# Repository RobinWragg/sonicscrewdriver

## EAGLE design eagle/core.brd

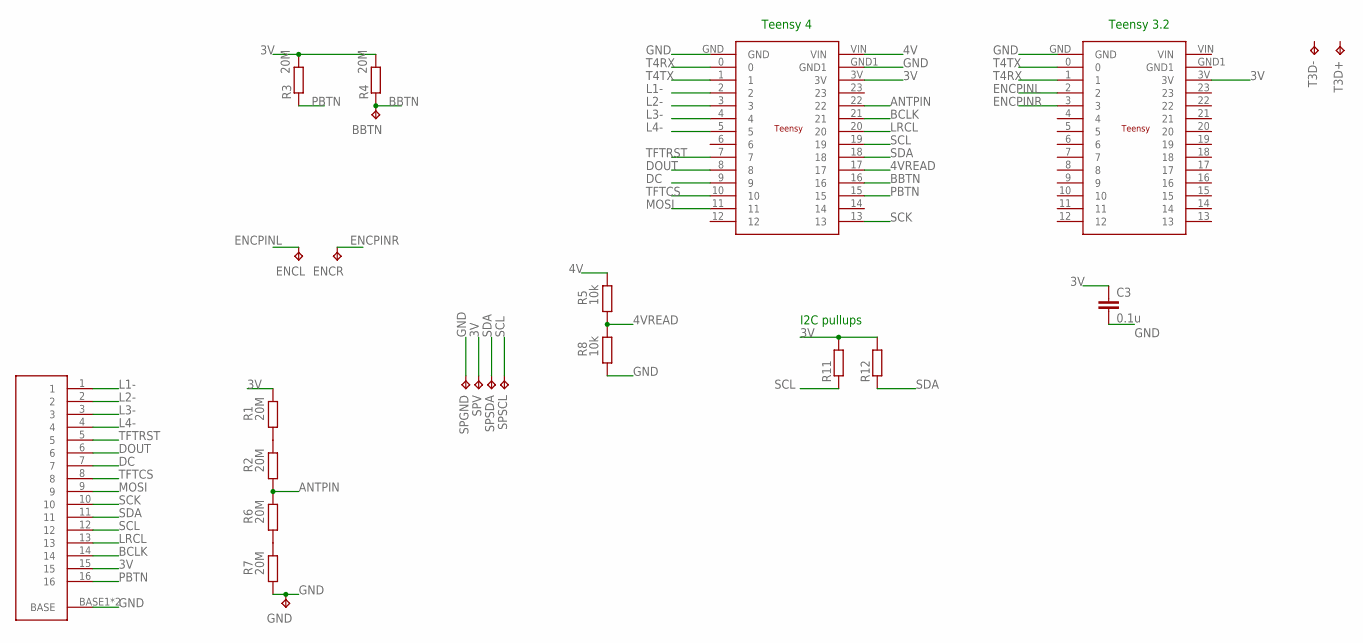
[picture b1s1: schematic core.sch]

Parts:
BBTN: TPTP14R; TP14R
C3: 0.1u; C0805
ENCL: TPTP14R; TP14R
ENCR: TPTP14R; TP14R
GND: TPTP14R; TP14R
R1, R2, R3, R4, R6, R7: 20M; M0805
R5, R8: 10k; M0805
R11, R12: R-EU_R0805; R0805
SPGND: TPTP14R; TP14R
SPSCL: TPTP14R; TP14R
SPSDA: TPTP14R; TP14R
SPV: TPTP14R; TP14R
T3D+, T3D-: TPTP14R; TP14R
U$1: TEENSY4; TEENSYSMALL
U$2: TEENSYSMALL
U$3: 16PINFFC

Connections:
3V: C3.1, R1.2, R3.2, R4.2, R11.2, R12.2, SPV.TP, U$1.3V, U$2.3V, U$3.15
4V: R5.2, U$1.VIN
4VREAD: R5.1, R8.2, U$1.17
ANTPIN: R2.1, R6.2, U$1.22
BBTN: BBTN.TP, R4.1, U$1.16
BCLK: U$1.21, U$3.14
DC: U$1.9, U$3.7
DOUT: U$1.8, U$3.6
ENCPINL: ENCL.TP, U$2.2
ENCPINR: ENCR.TP, U$2.3
GND: C3.2, GND.TP, R7.1, R8.1, SPGND.TP, U$1.GND, U$1.GND1, U$2.GND, U$3.BASE1 (BASE), U$3.BASE2 (BASE)
L1-: U$1.2, U$3.1
L2-: U$1.3, U$3.2
L3-: U$1.4, U$3.3
L4-: U$1.5, U$3.4
LRCL: U$1.20, U$3.13
MOSI: U$1.11, U$3.9
unnamed: R6.1, R7.2
unnamed: R1.1, R2.2
PBTN: R3.1, U$1.15, U$3.16
SCK: U$1.13, U$3.10
SCL: R11.1, SPSCL.TP, U$1.19, U$3.12
SDA: R12.1, SPSDA.TP, U$1.18, U$3.11
T4RX: U$1.0, U$2.1
T4TX: U$1.1, U$2.0
TFTCS: U$1.10, U$3.8
TFTRST: U$1.7, U$3.5

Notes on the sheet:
Teensy 4
Teensy 3.2
I2C pullups

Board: 2 copper layers, 24 parts (12 on the bottom side), 27 nets, no tracks yet.

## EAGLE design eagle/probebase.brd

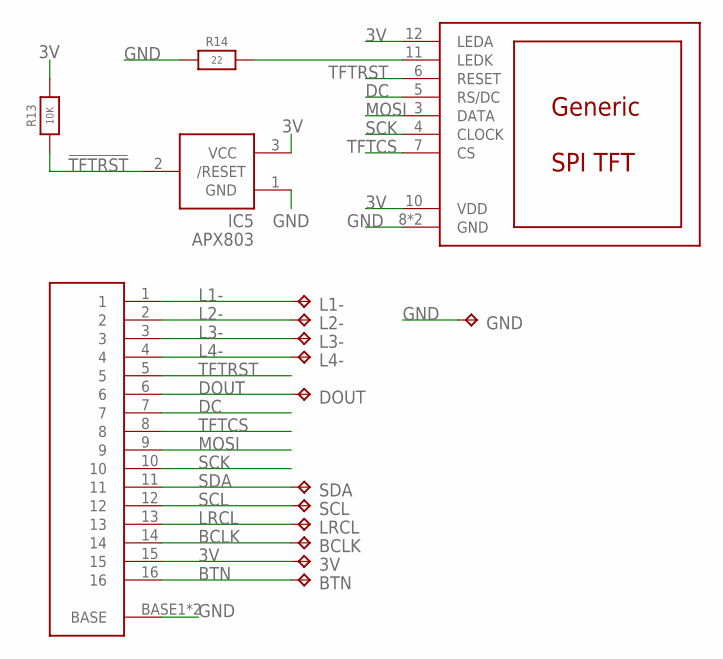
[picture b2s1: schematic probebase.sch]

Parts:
3V: TPTP14R; TP14R
BCLK: TPTP14R; TP14R
BTN: TPTP14R; TP14R
DOUT: TPTP14R; TP14R
GND: TPTP14R; TP14R
IC5: APX803; SOT23
L1-, L2-, L3-, L4-: TPTP14R; TP14R
LRCL: TPTP14R; TP14R
R13: 10K; 0603-NO
R14: 22; 0603-NO
SCL: TPTP14R; TP14R
SDA: TPTP14R; TP14R
U$3: 16PINFFC
U$4: TFT; MICROBUILDER_TFT_1.14IN_240X135_WRAPUNDER

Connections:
3V: 3V.TP, IC5.3 (VCC), R13.2, U$3.15, U$4.10 (VDD), U$4.12 (LEDA)
!TFTRST: IC5.2 (/RESET), R13.1
BCLK: BCLK.TP, U$3.14
BTN: BTN.TP, U$3.16
DC: U$3.7, U$4.5 (RS/DC)
DOUT: DOUT.TP, U$3.6
GND: GND.TP, IC5.1 (GND), R14.1, U$3.BASE1 (BASE), U$3.BASE2 (BASE), U$4.8 (GND), U$4.13 (GND)
L1-: L1-.TP, U$3.1
L2-: L2-.TP, U$3.2
L3-: L3-.TP, U$3.3
L4-: L4-.TP, U$3.4
LRCL: LRCL.TP, U$3.13
MOSI: U$3.9, U$4.3 (DATA)
unnamed: R14.2, U$4.11 (LEDK)
SCK: U$3.10, U$4.4 (CLOCK)
SCL: SCL.TP, U$3.12
SDA: SDA.TP, U$3.11
TFTCS: U$3.8, U$4.7 (CS)
TFTRST: U$3.5, U$4.6 (RESET)

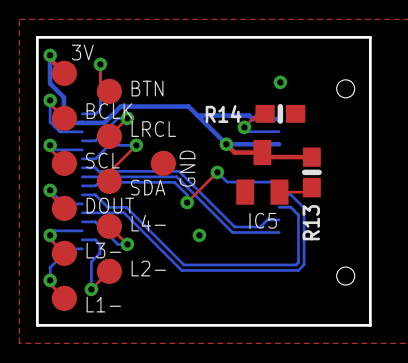
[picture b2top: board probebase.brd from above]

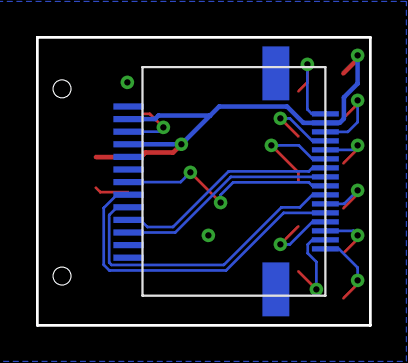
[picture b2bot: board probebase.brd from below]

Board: 2 copper layers, 18.5 x 16.0 mm, 17 parts (2 on the bottom side), 19 nets.

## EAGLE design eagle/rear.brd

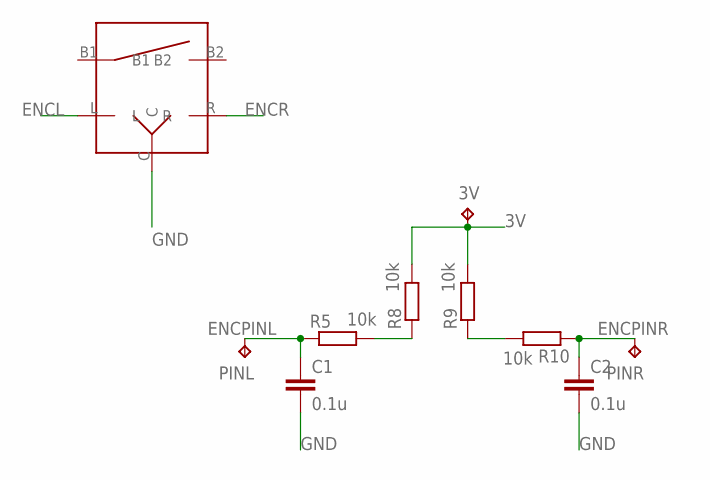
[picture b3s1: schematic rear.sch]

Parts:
3V: TPTP14R; TP14R
C1, C2: 0.1u; C0805
PINL: TPTP14R; TP14R
PINR: TPTP14R; TP14R
R5, R8, R9, R10: 10k; M0805
U$1: ENCODER

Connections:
3V: 3V.TP, R8.2, R9.2
ENCL: R5.2, R8.1, U$1.L
ENCPINL: C1.1, PINL.TP, R5.1
ENCPINR: C2.1, PINR.TP, R10.1
ENCR: R9.1, R10.2, U$1.R
GND: C1.2, C2.2, U$1.C

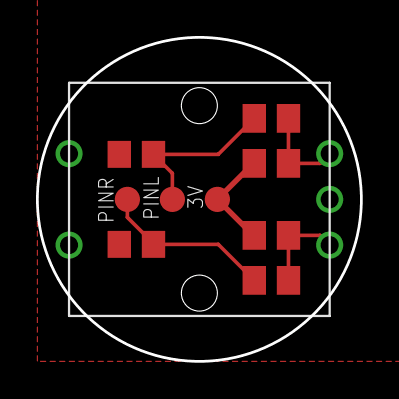
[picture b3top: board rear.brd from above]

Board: 2 copper layers, 18.0 x 18.0 mm, 10 parts (0 on the bottom side), 6 nets.

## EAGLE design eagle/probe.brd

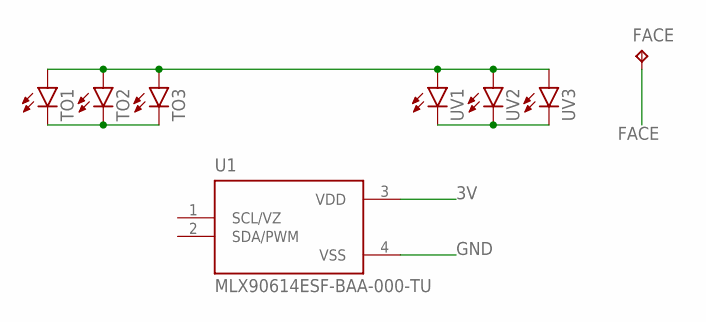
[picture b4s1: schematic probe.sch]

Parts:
FACE: TPTP14R; TP14R
TO1, TO2, TO3: LED5MM
U1: MLX90614ESF-BAA-000-TU; TO254P942H425-4
UV1, UV2, UV3: LED5MM

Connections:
3V: TO1.A, TO2.A, TO3.A, U1.3 (VDD), UV1.A, UV2.A, UV3.A
FACE: FACE.TP
GND: U1.4 (VSS)
unnamed: TO1.K (C), TO2.K (C), TO3.K (C)
unnamed: UV1.K (C), UV2.K (C), UV3.K (C)

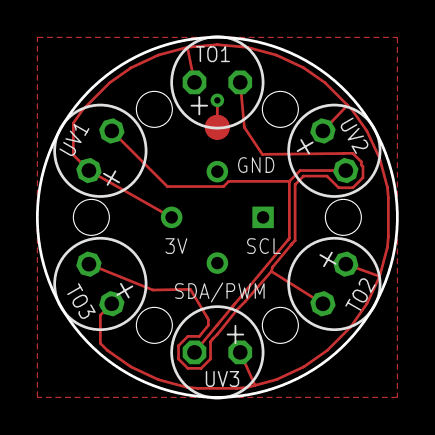
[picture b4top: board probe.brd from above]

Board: 2 copper layers, 20.0 x 20.0 mm, 8 parts (1 on the bottom side), 3 nets.

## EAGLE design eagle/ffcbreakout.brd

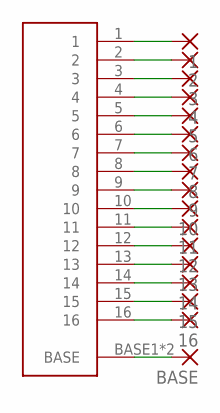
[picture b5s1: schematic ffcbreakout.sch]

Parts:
1, 2, 3, 4, 5, 6, 7, 8, 9, 10, 11, 12, 13, 14, 15, 16: 1,6/0,8
BASE: 1,6/0,8
U$1: 16PINFFC

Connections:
unnamed: 1.1, U$1.1
unnamed: 2.1, U$1.2
unnamed: 3.1, U$1.3
unnamed: 4.1, U$1.4
unnamed: 5.1, U$1.5
unnamed: 6.1, U$1.6
unnamed: 7.1, U$1.7
unnamed: 8.1, U$1.8
unnamed: 9.1, U$1.9
unnamed: 10.1, U$1.10
unnamed: 11.1, U$1.11
unnamed: 12.1, U$1.12
unnamed: 13.1, U$1.13
unnamed: 14.1, U$1.14
unnamed: 15.1, U$1.15
unnamed: 16.1, U$1.16
unnamed: BASE.1, U$1.BASE1 (BASE), U$1.BASE2 (BASE)

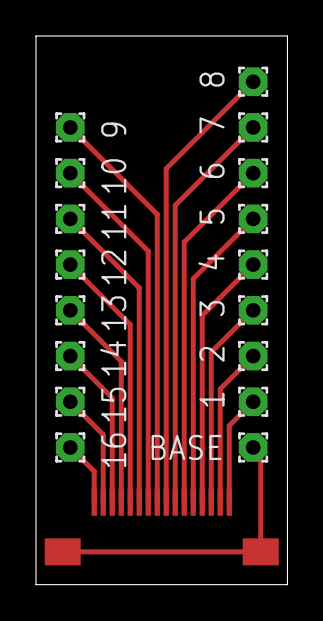
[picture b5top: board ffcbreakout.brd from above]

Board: 2 copper layers, 14.0 x 30.5 mm, 18 parts (0 on the bottom side), 17 nets.

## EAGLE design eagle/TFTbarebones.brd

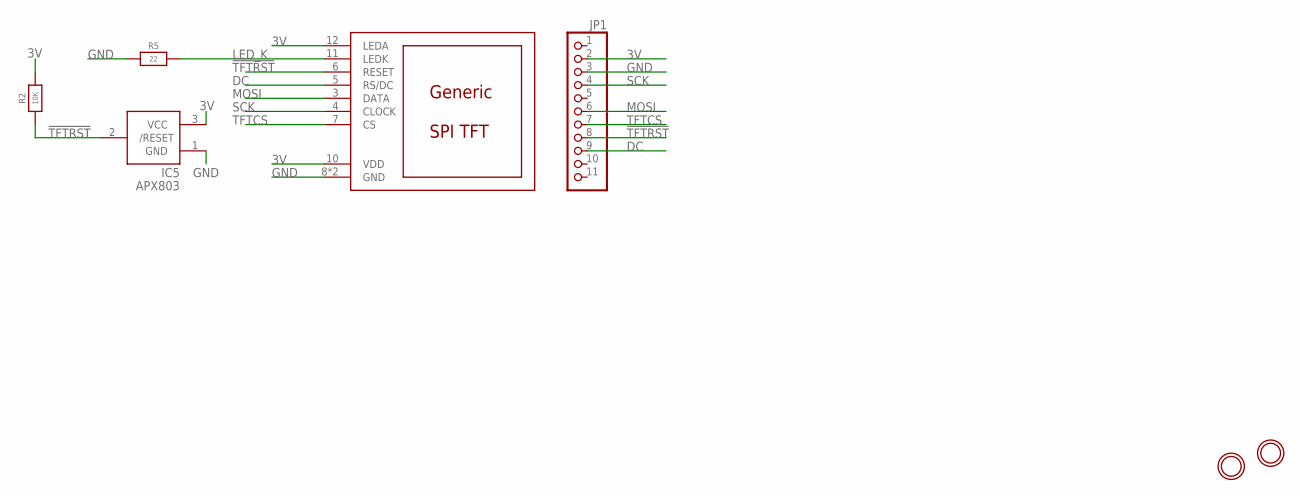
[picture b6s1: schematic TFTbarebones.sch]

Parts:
DISP1: DISP_LCD_GENERIC_SPI_1.14IN_240X135_WRAPUNDER; TFT_1.14IN_240X135_WRAPUNDER
IC5: APX803; SOT23
JP1: HEADER-1X11; 1X11_ROUND
R2: 10K; 0603-NO
R5: 22; 0603-NO
U$9, U$10: MOUNTINGHOLE2.5; MOUNTINGHOLE_2.5_PLATED

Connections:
3V: DISP1.10 (VDD), DISP1.12 (LEDA), IC5.3 (VCC), JP1.2, R2.2
!TFTRST: DISP1.6 (RESET), IC5.2 (/RESET), JP1.8, R2.1
DC: DISP1.5 (RS/DC), JP1.9
GND: DISP1.8 (GND), DISP1.13 (GND), IC5.1 (GND), JP1.3, R5.1
LED_K: DISP1.11 (LEDK), R5.2
MOSI: DISP1.3 (DATA), JP1.6
SCK: DISP1.4 (CLOCK), JP1.4
TFTCS: DISP1.7 (CS), JP1.7

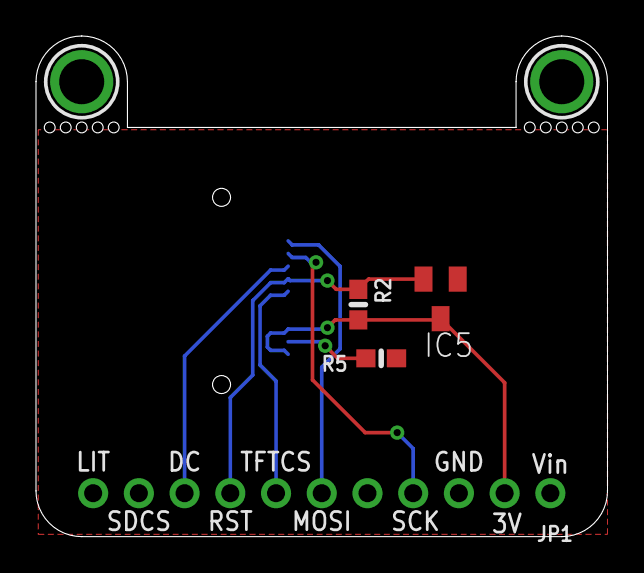
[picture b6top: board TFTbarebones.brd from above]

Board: 2 copper layers, 31.8 x 27.8 mm, 7 parts (1 on the bottom side), 8 nets.

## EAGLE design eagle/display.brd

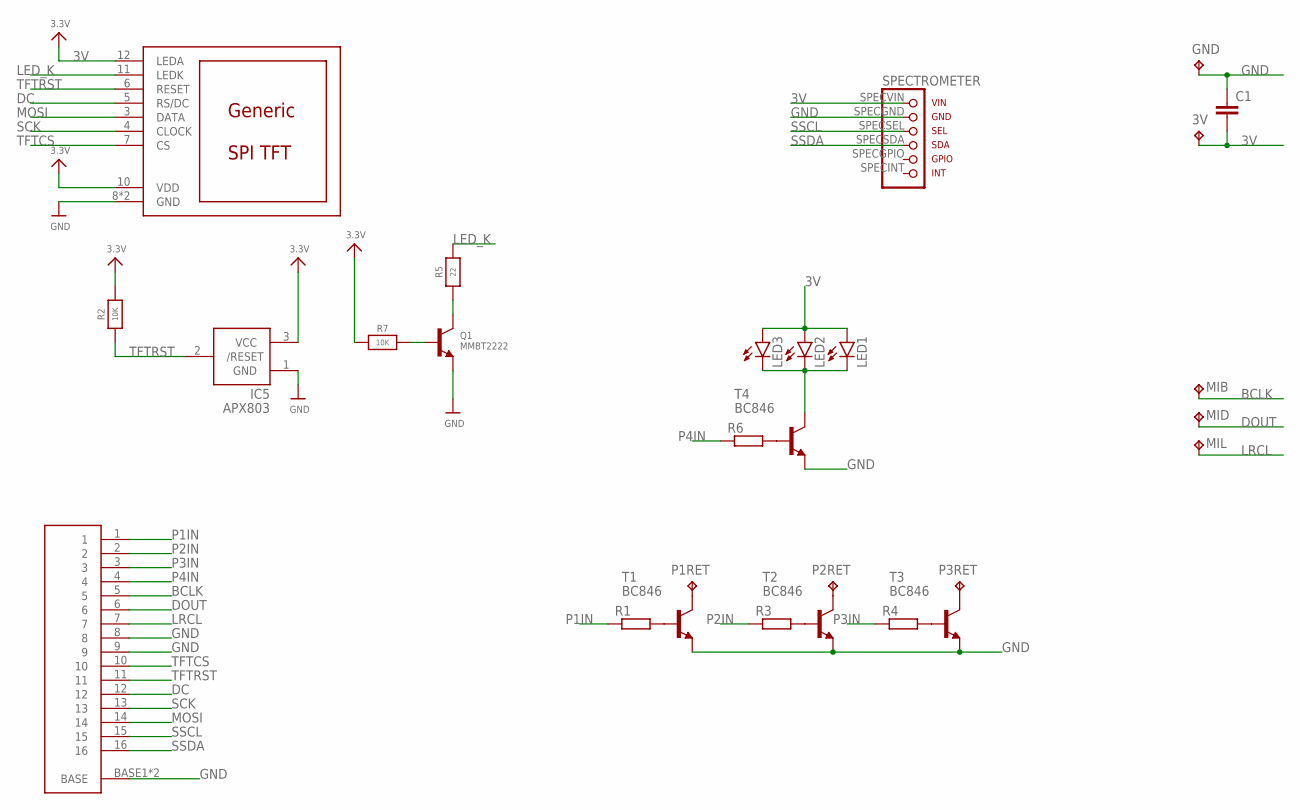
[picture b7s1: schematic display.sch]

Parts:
3V: TPTP20R; TP20R
C1: C-EUC0805; C0805
DISP1: DISP_LCD_GENERIC_SPI_1.14IN_240X135_WRAPUNDER; TFT_1.14IN_240X135_WRAPUNDER
GND: TPTP20R; TP20R
IC5: APX803; SOT23
LED1, LED2, LED3: LED3MM
MIB: TPTP10R; TP10R
MID: TPTP10R; TP10R
MIL: TPTP10R; TP10R
P1RET, P2RET, P3RET: TPTP10R; TP10R
Q1: MMBT2222; SOT23-WIDE
R1, R3, R4, R6: R-EU_R0805; R0805
R2, R7: 10K; 0603-NO
R5: 22; 0603-NO
T1, T2, T3, T4: BC846; SOT23
U$2: SPECTROMETER
U$3: 16PINFFC

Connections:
3V: 3V.TP, C1.2, DISP1.10 (VDD), DISP1.12 (LEDA), IC5.3 (VCC), LED1.A, LED2.A, LED3.A, R2.2, R7.1, U$2.SPECVIN
BCLK: MIB.TP, U$3.5
DC: DISP1.5 (RS/DC), U$3.12
DOUT: MID.TP, U$3.6
GND: C1.1, DISP1.8 (GND), DISP1.13 (GND), GND.TP, IC5.1 (GND), Q1.2 (E), T1.2 (E), T2.2 (E), T3.2 (E), T4.2 (E), U$2.SPECGND, U$3.8, U$3.9, U$3.BASE1 (BASE), U$3.BASE2 (BASE)
LED_K: DISP1.11 (LEDK), R5.2
LRCL: MIL.TP, U$3.7
MOSI: DISP1.3 (DATA), U$3.14
unnamed: Q1.1 (B), R7.2
unnamed: R1.2, T1.1 (B)
unnamed: Q1.3 (C), R5.1
unnamed: R3.2, T2.1 (B)
unnamed: R4.2, T3.1 (B)
unnamed: P1RET.TP, T1.3 (C)
unnamed: P2RET.TP, T2.3 (C)
unnamed: P3RET.TP, T3.3 (C)
unnamed: R6.2, T4.1 (B)
P1IN: R1.1, U$3.1
P2IN: R3.1, U$3.2
P3IN: R4.1, U$3.3
P4IN: R6.1, U$3.4
PWM4: LED1.K (C), LED2.K (C), LED3.K (C), T4.3 (C)
SCK: DISP1.4 (CLOCK), U$3.13
SSCL: U$2.SPECSEL, U$3.15
SSDA: U$2.SPECSDA, U$3.16
TFTCS: DISP1.7 (CS), U$3.10
TFTRST: DISP1.6 (RESET), IC5.2 (/RESET), R2.1, U$3.11

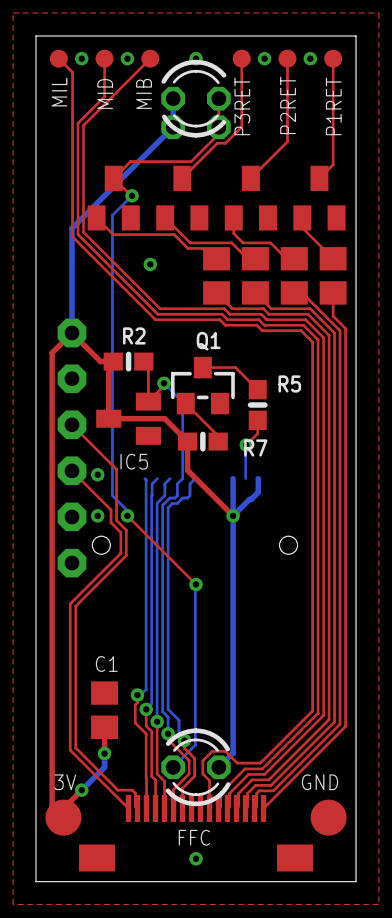
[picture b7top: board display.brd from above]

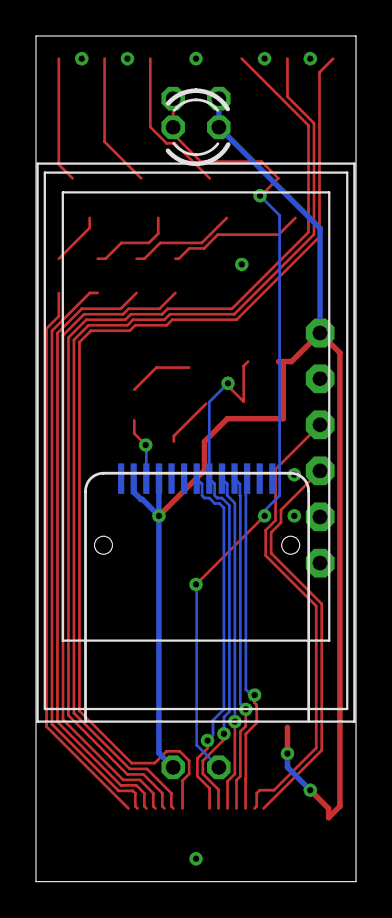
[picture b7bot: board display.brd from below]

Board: 2 copper layers, 17.8 x 47.0 mm, 28 parts (3 on the bottom side), 27 nets.

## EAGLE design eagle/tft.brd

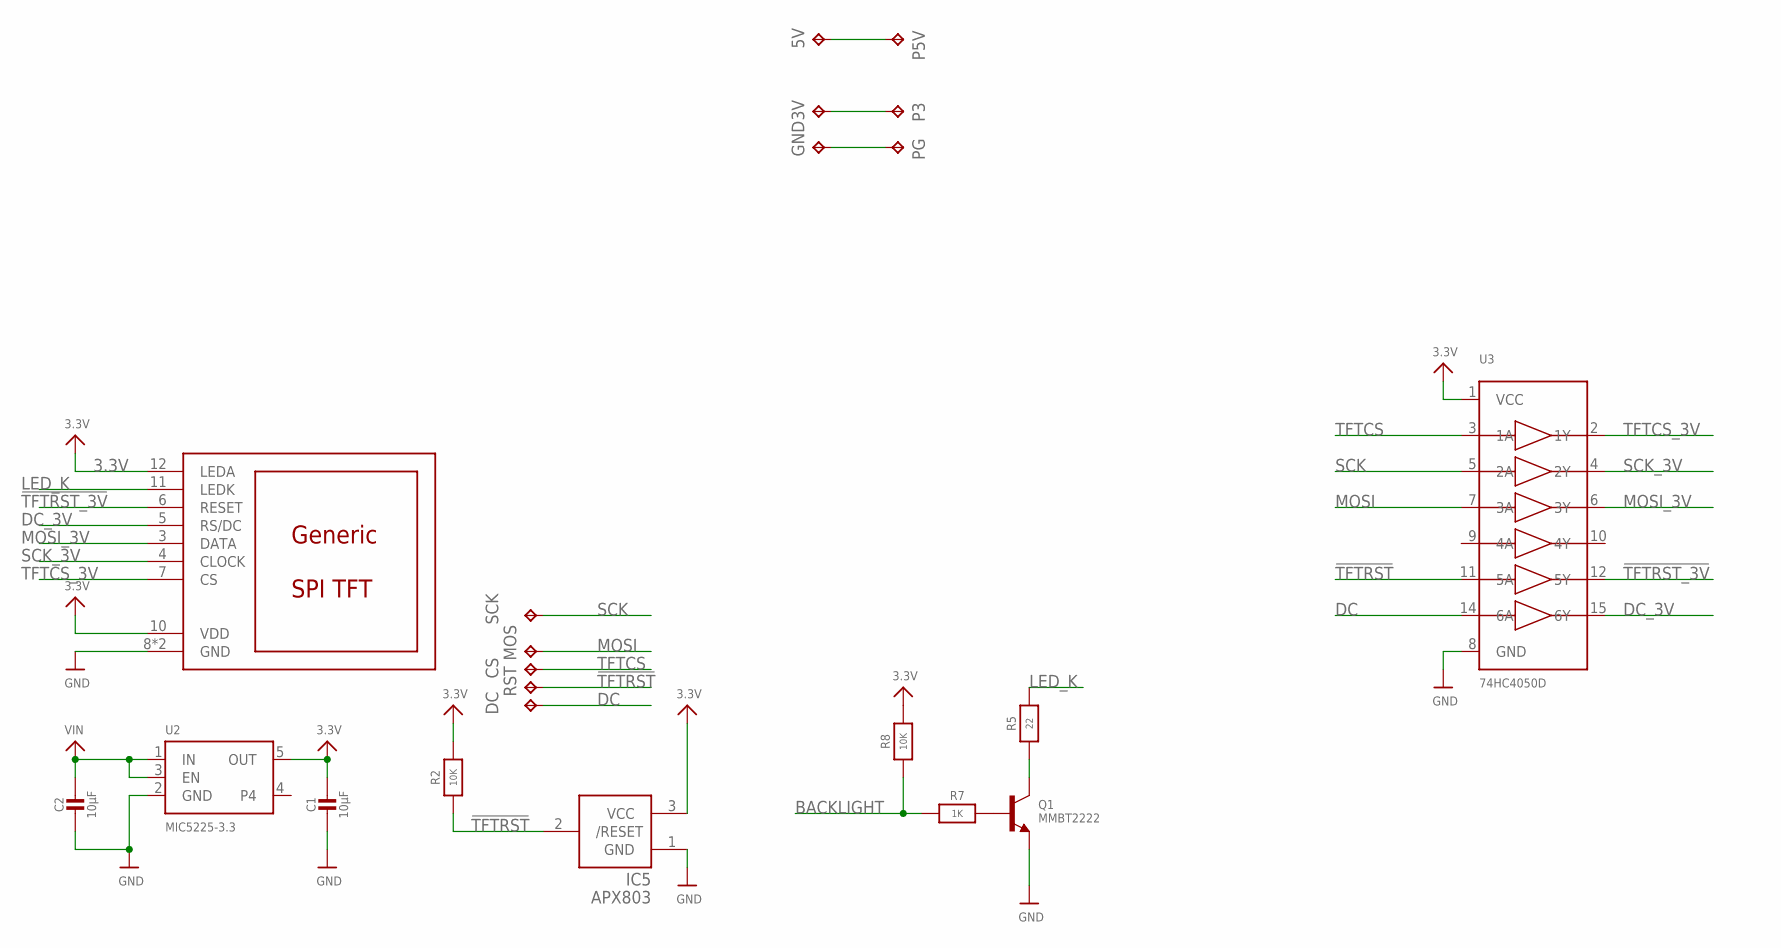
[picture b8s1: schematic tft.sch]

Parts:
3V, 5V: TPB1,27; B1,27
C1, C2: 10µF; 0805-NO
CS: TPB1,27; B1,27
DC: TPB1,27; B1,27
DISP1: DISP_LCD_GENERIC_SPI_1.14IN_240X135_WRAPUNDER; TFT_1.14IN_240X135_WRAPUNDER
GND: TPB1,27; B1,27
IC5: APX803; SOT23
MOS: TPB1,27; B1,27
P3, P5V: TPB1,27; B1,27
PG: TPB1,27; B1,27
Q1: MMBT2222; SOT23-WIDE
R2, R8: 10K; 0603-NO
R5: 22; 0603-NO
R7: 1K; 0603-NO
RST: TPB1,27; B1,27
SCK: TPB1,27; B1,27
U2: MIC5225-3.3; SOT23-5
U3: 74HC4050D; SOIC16

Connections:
3.3V: C1.1, DISP1.10 (VDD), DISP1.12 (LEDA), IC5.3 (VCC), R2.2, R8.2, U2.5 (OUT), U3.1 (VCC)
!TFTRST: IC5.2 (/RESET), R2.1, RST.TP, U3.11 (5A)
!TFTRST_3V: DISP1.6 (RESET), U3.12 (5Y)
BACKLIGHT: R7.1, R8.1
DC: DC.TP, U3.14 (6A)
DC_3V: DISP1.5 (RS/DC), U3.15 (6Y)
GND: C1.2, C2.2, DISP1.8 (GND), DISP1.13 (GND), GND.TP, IC5.1 (GND), PG.TP, Q1.2 (E), U2.2 (GND), U3.8 (GND)
LED_K: DISP1.11 (LEDK), R5.2
MOSI: MOS.TP, U3.7 (3A)
MOSI_3V: DISP1.3 (DATA), U3.6 (3Y)
unnamed: Q1.1 (B), R7.2
unnamed: 5V.TP, P5V.TP
unnamed: Q1.3 (C), R5.1
SCK: SCK.TP, U3.5 (2A)
SCK_3V: DISP1.4 (CLOCK), U3.4 (2Y)
TFTCS: CS.TP, U3.3 (1A)
TFTCS_3V: DISP1.7 (CS), U3.2 (1Y)
VIN: 3V.TP, C2.1, P3.TP, U2.1 (IN), U2.3 (EN)

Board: 2 copper layers, 22 parts (1 on the bottom side), 18 nets, no tracks yet.

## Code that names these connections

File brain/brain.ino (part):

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#define ACCENT_PWM_PIN (5)
// 6
#define TFT_RST_PIN (7)
#define DOUT_PIN (8)
#define TFT_DC_PIN (9)
#define TFT_CS_PIN (10)
#define TFT_MOSI_PIN (11)
// 12
#define TFT_SCK_PIN (13)
// 14
#define BBTN_PIN (15)
#define PBTN_PIN (16)
#define VOLTREAD_PIN (17)
#define SDA_PIN (18)
#define SCL_PIN (19)
#define BCLK_PIN (20)
#define ANTENNA_PIN (22)
#define UNAVAILABLE_PIN (23)

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
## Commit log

2020-11-07 initial
2020-11-07 gitignore etc
2020-11-07 audio out files
2020-11-09 Initial teensy3.2+teensy4.0
2020-11-10 added teensy pinouts
2020-11-10 PDFs
2020-11-12 add eagle files
2020-11-14 start core pcb
2020-11-15 add torch and uv schematic
2020-11-15 serial comms
2020-11-16 digitalWrite workaround
2020-11-16 add laser, start probe demo
2020-11-16 add mic to probe demo
2020-11-23 probe pcb v1
2020-12-05 datasheets
2020-12-05 change uv,torch, and laser pins
2020-12-05 removed bme680 stuff
2020-12-05 implemented volume control
2020-12-05 Add PWM_MAX
2020-12-05 tidied
2020-12-05 Smarter teensy3 access speed
2020-12-09 Fix probe pcb bug
2020-12-10 Added source TFT eagle files
2020-12-11 Added laser mount to probe pcb (v2)
2020-12-12 began rear pcb
2020-12-15 Tweaked antenna stuff
2020-12-15 Updated probe and rear eagle files
2020-12-15 Tweaked probe LED traces
2020-12-16 new pcbs
2020-12-17 Display board redesigned with FFC connector
2020-12-20 ffc breakout and core changes
2020-12-20 20mm probe pcb
2020-12-20 created low-profile TFT SMD
2020-12-20 mini probe
2020-12-20 mini probe redesign
2020-12-22 probe base
2020-12-22 probe: better ground plane
2020-12-22 Re-organise eagle folder
2020-12-24 full probe demo except for lights and antenna
2020-12-24 decided on ffc wire layout.
2020-12-24 First order of probe, probebase and FFC breakout PCBs for 22mm enclosure
2020-12-26 core pcb improvements
2020-12-29 Encoder eagle part
2020-12-31 Added optional I2C pullups and started renderer.
2021-01-02 Added text.c
2021-01-07 Fixed ffc connector dimensions
2021-01-08 Redesigned probe base pcb
2021-01-08 added encoder to rear pcb
2021-01-11 Added capacitor between 3v and gnd on core pcb
2021-01-13 Experimental fix for tft crash.
2021-02-06 misc pcb changes
2021-02-07 Made a note of MOSI
2021-02-07 Added tft test
2021-02-25 Better test code
2021-02-26 all the things
2021-02-26 core is now 18mm
2021-03-11 Added altimeter code
2021-03-12 altimeter fix and tabs formatting
2021-03-21 Added explicit disabling of internal I2C pullups. Might be overridden in library though.
2022-10-22 Spectrometer stuff
2022-10-22 Remove almost all of altimeter, gyro etc
